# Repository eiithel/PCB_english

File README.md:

#**Introduction**  
There is currently no cure for autism. Special educators often struggle to communicate with children
sometimes immured in their silence. Autistic children can develop their language and facilitate their
interpersonal interactions with the help of early childhood management and special education.   
According to recent studies, the robot is a relevant tool for reducing some autistic symptoms, such as
joint attention deficit disorder. It also promotes generalization of skills.   
I proposed a new hardware and software architecture for Leka's first educational robot, as an extension
to its control system. This new architecture is based on a Linux kernel.   
This expansion provides support for experimentation and verification of embedded Linux applications
for a robotic base.    
**Key words**: robotics, autism, hardware conception, embedded linux

##**Functional requirements**

This card has been developed for the purpose of writing code at rapid speeds. It isn't the final version of Moti but it will be rather useful for developers, helping them to realize their tests and to validate this type of architecture. The card allows connection between `actuators` that permits the robot to live and to move and there are also `sensors` that permit the robot to be aware of its environment and to react consequential to that environment.

* Actuators
  * Motor control
  * RGB LEDs control
*  Datas/Sensoring
  *  Accelerometer/gyroscope
  *  Microphone

_the video is not supported in this version._

##**Components choice**

###Control part

* **Teensy 3.1**  

The control card is equipped with a __Teensy__ ARM Cortex 32 bits, a powerfull 32 bits MCU.   
This module is suitable for `C/C++` programming and is compatible with code written for __Arduino__. It is also featured with a large number of IO pinouts (_total of 34_). The Teensy is dedicated to three tasks :

*  Communicate to the __Arietta__ informations concerning the differents modules/sensors and to manage the different requests.
* To deploy 12 GPIO and one serial port.
* To Manage enslavement motor calculations.

>The code written on this card doesn't have to be modified. It should have just the simpliest code possible.
.

   * **Arietta**  

The __Arietta__ is a little embedded linux system based on a very swift ARM9. (_400MHZ_) it is equipped with a WIFI module, several GPIOs and a serial port connected to the __Teensy__. This comprises the central intelligence of the robot and is dedicated to several tasks :

  * To receive and to send information and requests to the __Teensy__.
  * To manage all Moti's intelligence. (_This part can be developped on a computer before being embedded on the card_).
  * Web server in order to develop applications permitting a certain number of clients to use its services (_Smartphones and tablets_).

>An Arietta's i2C bus is available on the card to add eventual sensor.   

A simple example of how to communicate beetween Arietta and Teensy :  
<https://github.com/eiithel/node_Serial>   
I used NodeJS for my tests.

###Motors

Motors are controlled by the control card but they need a dedicated integrated circuit to supply them enough power in order to run correctly. This is what permits the POLULU module based on a __TB6612FNG__ chip.

PWMs and logic (AIN, BIN) are provided by the **Teensy**.

You can see a use case here: <https://github.com/eiithel/motors_test>    

>Be carefull. The **Teensy** is provided by 3 Timers.  
Motors PWMs come from **Timer0** but this timer is already used for **GSCLK** and **SIN** signals of the **TLC** due to pin sharing.  
You have to replace this PWMs by Outputs provided by Timer2 which is not used.  
This Timer is located under the **Teensy** (_pins 25 & 32_).

### **RGB LEDs**

In order to pilot 6 RGB LEDs, we need 6*3 = 18 channels. It is out of the question to use all the PWM Teensy outputs for that. The trick is to use a LED's driver that will allow us to increase our number of avalaible PWM outputs. This driver is controlled by the i2C Bus and provids 16 PWM channels. The 2 missing channels will be provided by the Teensy itself. The used component is the __TLC5940__ (Texas Instrument).

You can see a use case here: <https://github.com/eiithel/TLC4950_test>

##**Supplies**

The robot is designed with separate voltage regulators for digital and analog supply.   
The control part of the architecture needs to be supplied by 5V. The motor and its components need 6V. The solution was to use DC/DC adjustable regulators in order to provide good tensions scales.

**PTN78000WAH** _(Texas Instrument)_

This component can supply a max output current of 3A which is enough to run motors. It works for a 7 to 36V wide input tension. It permits to obtain a 2.5 to 22V wide output regulate tension. The output voltage is set using a single external resistor.

* 21 kohm for `5V`
* 13 kohm for `6V`
 
>All the passive components of the circuit are _SMD_ in order to save space on the board.

__BE CAREFULL__

This input is not protected against over and reverse voltages.  
When supplying the board take care to not invert anode and cathode. It would cause irreversible damages to the whole board.

###**A little display of the card**

> <center>_Bottom face_</center>

><center>_Top face_</center>

###__Bloc diagram__

To sum up, here is the electronical architecture of the prototype:

--
And the final view with some little errors to correct:   

<center>_Final view_</center>

> Written by Eiithel.

<a href="https://fr.linkedin.com/pub/ethel-marquer/84/151/485" style="text-decoration:none;"><span style="font: 80% Arial,sans-serif; color:#0783B6;">&nbsp;Voir le profil de Ethel Marquer</span></a>

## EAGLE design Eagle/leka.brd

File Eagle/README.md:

#Instructions

In the `lb` repertory you can find all the libraries used for the pcb design.

*   robot_insa_V1.lbr for __AriettaG25__
*   Teensy3.0.lbr for __Teensy__
*   TI-Eagle_library.lbr for __PTN78000WAH__
*   TLC5940.lbr for the __TLC__

Eagle files are located in the `Eagle` reportory.

* `leka.sch` is the schematic, this file represents the circuit diagram.
Parts are placed on many sheets and are connected together through ports.

* `leka.brd` represents the "_physical_" PCB. In this file, traces are connected 
besides the connections defined in the schematic.   
The auto-route function didn't 
have been used because the optimisation is worst with this method.  
Take the time to realize your own routes. Mountage will be easier!

> A little display of .brd file

-----
-----

>If you order this PCB from a PCB manufacturer, **DON'T** ask for serigraphy.
Indeed, there is a lot of "stop mask" issues during DRC checking and this problem can be simply resolved by deleting this layer. 
The explanation is that Serigraphy layer prints onto top or bottom copper and that isn't correct.

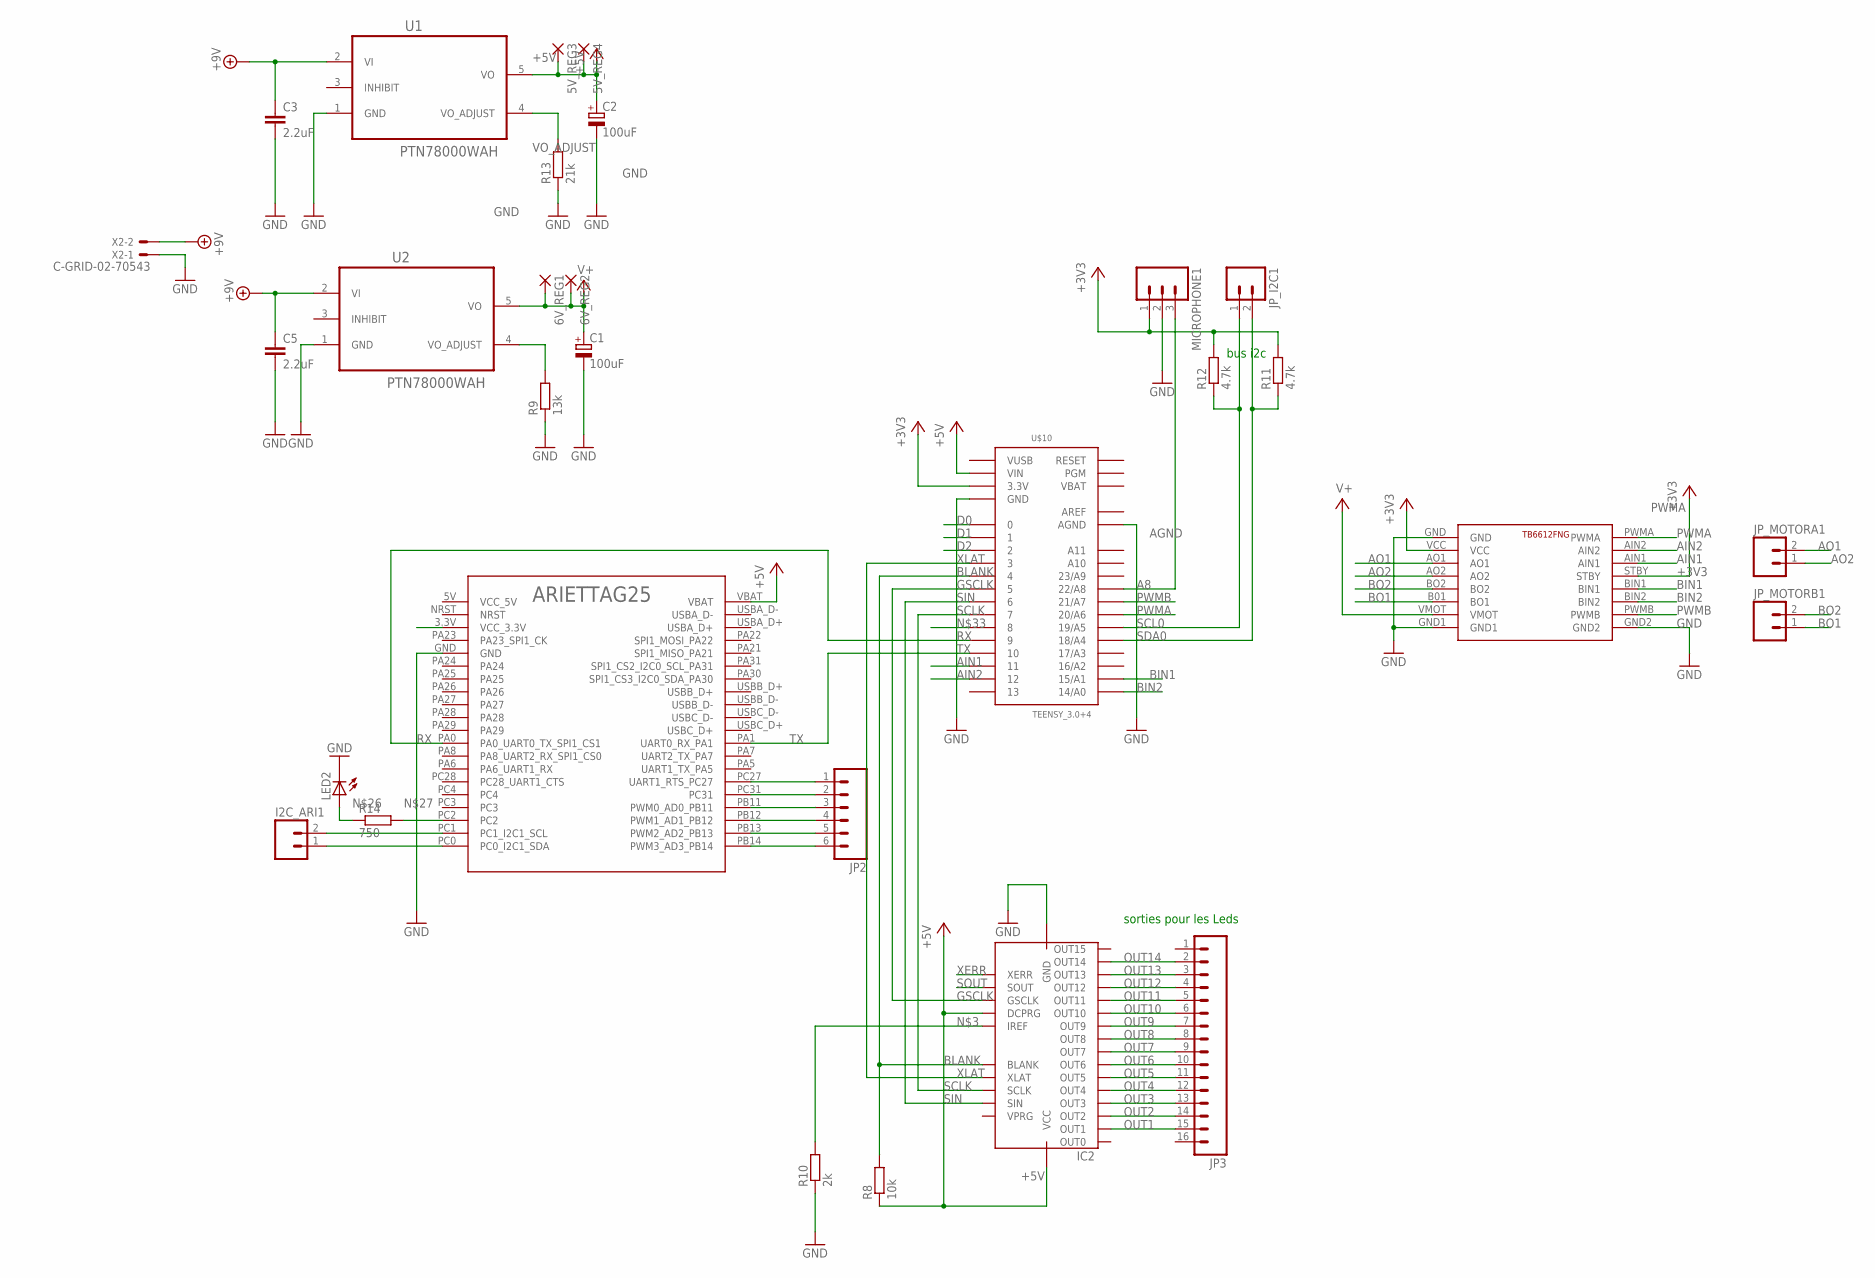
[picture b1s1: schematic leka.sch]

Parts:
5V_REG3, 5V_REG4, 6V_REG1, 6V_REG2: 2,54/0,9
C1, C2: 100uF; E2-5
C3, C5: 2.2uF; C0805
I2C_ARI1: M02LOCK_LONGPADS; 1X02_LOCK_LONGPADS
IC2: IC-PACKAGE_DIL28-3
JP2: M06SILK_FEMALE_PTH; 1X06
JP3: M16LONGPADS; 1X16_LONGPADS
JP_I2C1: M02LOCK_LONGPADS; 1X02_LOCK_LONGPADS
JP_MOTORA1: M02JST-PTH-2; JST-2-PTH
JP_MOTORB1: M02JST-PTH-2; JST-2-PTH
LED2: LEDSML0805; SML0805
MICROPHONE1: M03PTH; 1X03
R8: 10k; M0805
R9: 13k; M0805
R10: 2k; M0805
R11, R12: 4.7k; M0805
R13: 21k; M0805
R14: 750; M0805
U1, U2: PTN78000WAH; TI_PTN78000WAH
U$2: ARIETTAG25/256; ARIETTAG25
U$6: TB6612FNG; MOTOR_DRIVER
U$10: TEENSY_3.0+4
X2: C-GRID-02-70543; 70543-02

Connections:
+3V3: MICROPHONE1.1, R11.2, R12.2, U$6.STBY, U$6.VCC, U$10.3.3V, U$10.3.3V1 (3.3V)
+5V: 5V_REG3.1, 5V_REG4.1, C2.+, IC2.19 (DCPRG), IC2.21 (VCC), R8.1, U1.5 (VO), U$2.VBAT, U$10.VIN
+9V: C3.1, C5.1, U1.2 (VI), U2.2 (VI), X2.2
A8: MICROPHONE1.3, U$10.22/A8
AGND: U$10.AGND
AIN1: U$6.AIN1, U$10.11
AIN2: U$6.AIN2, U$10.12
AO1: JP_MOTORA1.2, U$6.AO1
AO2: JP_MOTORA1.1, U$6.AO2
AREF: U$10.AREF
BIN1: U$6.BIN1, U$10.15/A1
BIN2: U$6.BIN2, U$10.14/A0
BLANK: IC2.23 (BLANK), R8.2, U$10.4
BO1: JP_MOTORB1.1, U$6.B01 (BO1)
BO2: JP_MOTORB1.2, U$6.BO2
D0: U$10.0
D1: U$10.1
D2: U$10.2
GND: C1.-, C2.-, C3.2, C5.2, IC2.22 (GND), LED2.C, MICROPHONE1.2, R9.1, R10.1, R13.1, U1.1 (GND), U2.1 (GND), U$2.GND, U$6.GND, U$6.GND1, U$6.GND2, U$10.GND, U$10.GND1 (GND), X2.1
GSCLK: IC2.18 (GSCLK), U$10.5
unnamed: IC2.20 (IREF), R10.2
unnamed: I2C_ARI1.1, U$2.PC0 (PC0_I2C1_SDA)
unnamed: I2C_ARI1.2, U$2.PC1 (PC1_I2C1_SCL)
unnamed: R9.2, U2.4 (VO_ADJUST)
unnamed: JP2.6, U$2.PB14 (PWM3_AD3_PB14)
unnamed: JP2.5, U$2.PB13 (PWM2_AD2_PB13)
unnamed: JP2.4, U$2.PB12 (PWM1_AD1_PB12)
unnamed: JP2.2, U$2.PC31
unnamed: JP2.1, U$2.PC27 (UART1_RTS_PC27)
unnamed: JP2.3, U$2.PB11 (PWM0_AD0_PB11)
unnamed: LED2.A, R14.1
unnamed: R14.2, U$2.PC2
OUT1: IC2.1 (OUT1), JP3.15
OUT2: IC2.2 (OUT2), JP3.14
OUT3: IC2.3 (OUT3), JP3.13
OUT4: IC2.4 (OUT4), JP3.12
OUT5: IC2.5 (OUT5), JP3.11
OUT6: IC2.6 (OUT6), JP3.10
OUT7: IC2.7 (OUT7), JP3.9
OUT8: IC2.8 (OUT8), JP3.8
OUT9: IC2.9 (OUT9), JP3.7
OUT10: IC2.10 (OUT10), JP3.6
OUT11: IC2.11 (OUT11), JP3.5
OUT12: IC2.12 (OUT12), JP3.4
OUT13: IC2.13 (OUT13), JP3.3
OUT14: IC2.14 (OUT14), JP3.2
PWMA: U$6.PWMA, U$10.20/A6
PWMB: U$6.PWMB, U$10.21/A7
RX: U$2.PA0 (PA0_UART0_TX_SPI1_CS1), U$10.9
SCL0: JP_I2C1.1, R12.1, U$10.19/A5
SCLK: IC2.25 (SCLK), U$10.7
SDA0: JP_I2C1.2, R11.1, U$10.18/A4
SIN: IC2.26 (SIN), U$10.6
SOUT: IC2.17 (SOUT)
TX: U$2.PA1 (UART0_RX_PA1), U$10.10
V+: 6V_REG1.1, 6V_REG2.1, C1.+, U2.5 (VO), U$6.VMOT
VBAT: U$10.VBAT
VCC_5V: U$2.5V (VCC_5V)
VO_ADJUST: R13.2, U1.4 (VO_ADJUST)
VUSB: U$10.VUSB
XERR: IC2.16 (XERR)
XLAT: IC2.24 (XLAT), U$10.3

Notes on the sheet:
sorties pour les Leds
bus i2c

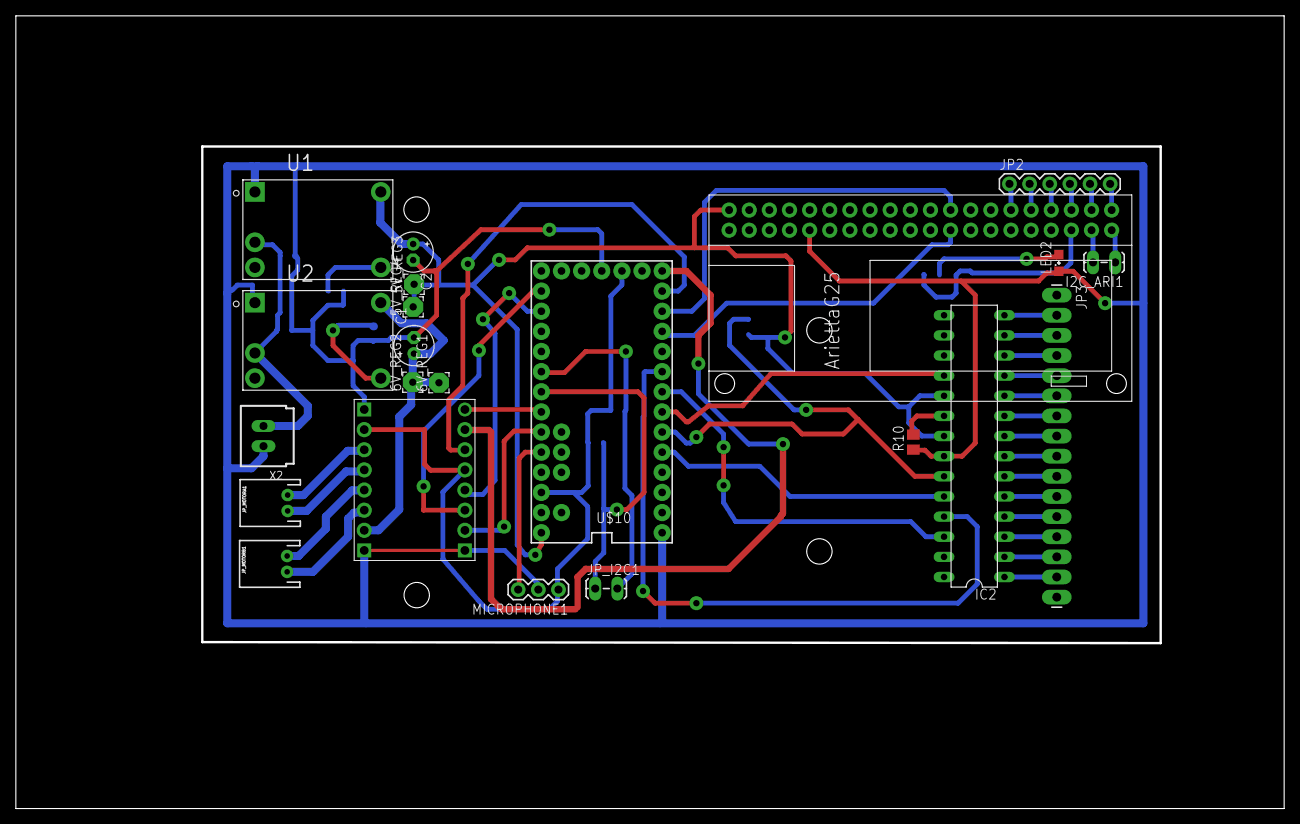
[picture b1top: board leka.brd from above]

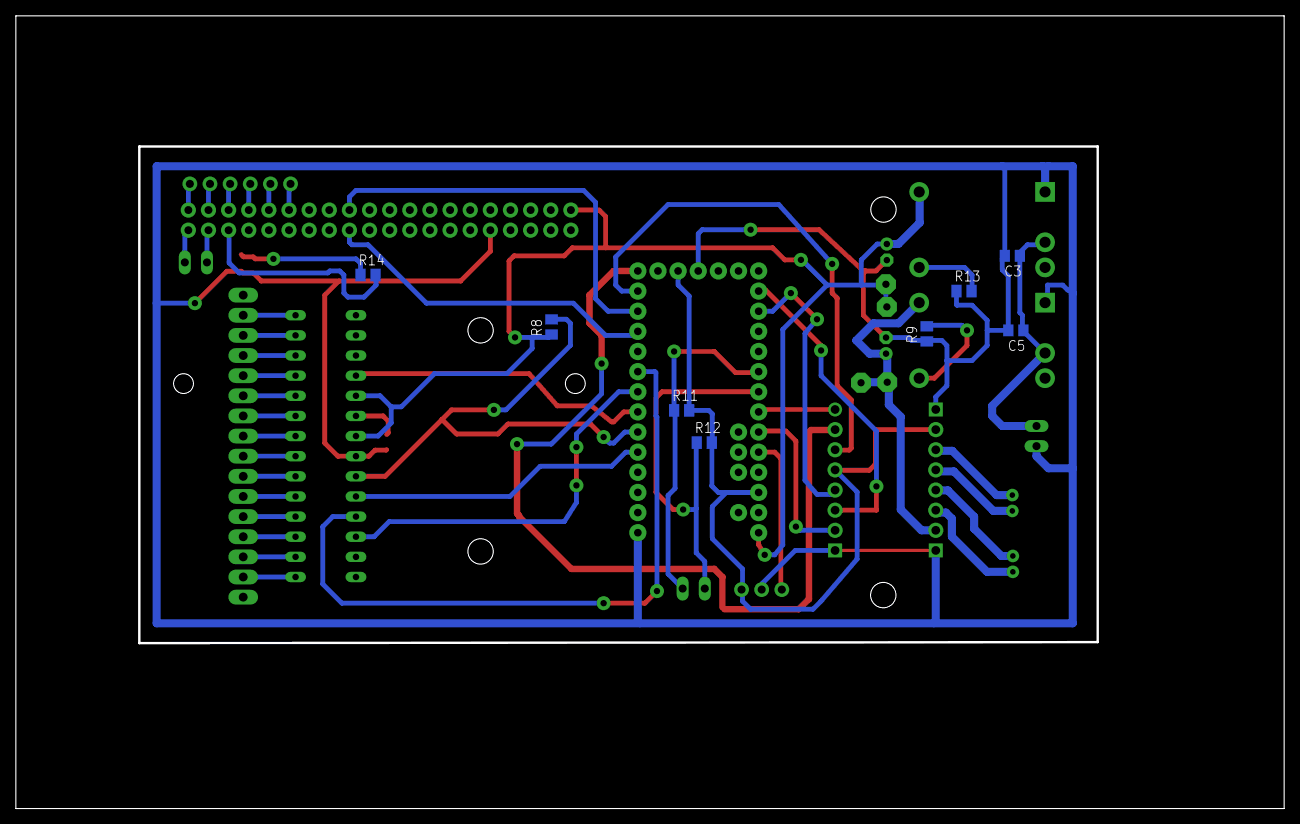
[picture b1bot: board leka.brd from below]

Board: 2 copper layers, 159.7 x 99.7 mm, 30 parts (8 on the bottom side), 52 nets.

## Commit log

2015-08-13 Published with https://stackedit.io/
2015-08-13 Image repertory creation
2015-08-18 add Eagle files
2015-08-18 librairies files added
2015-08-18 Rename instructions.md
2015-08-18 Images added for brd and sch
2015-08-18 Update REAME with addetion of Images
2015-08-18 deletion of sch image
2015-08-18 Correction README
2015-08-18 Image added
2015-08-21 Datasheets added
2015-08-24 Update Images
2015-10-07 add Image

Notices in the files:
parts and their libraries:
SparkFun-Connectors: Licensing: Creative Commons ShareAlike 4.0 International - https://creativecommons.org/licenses/by-sa/4.0
